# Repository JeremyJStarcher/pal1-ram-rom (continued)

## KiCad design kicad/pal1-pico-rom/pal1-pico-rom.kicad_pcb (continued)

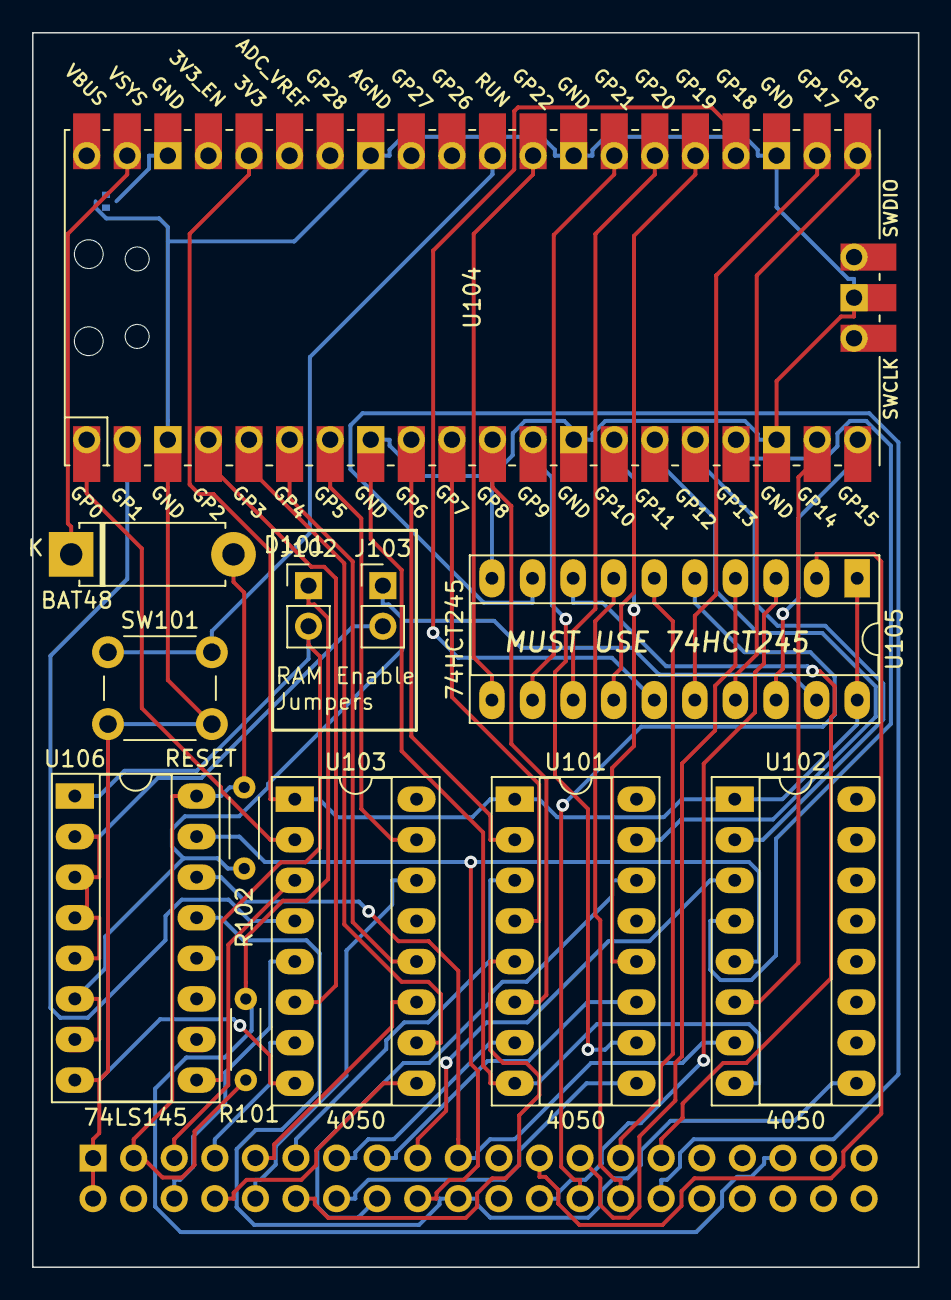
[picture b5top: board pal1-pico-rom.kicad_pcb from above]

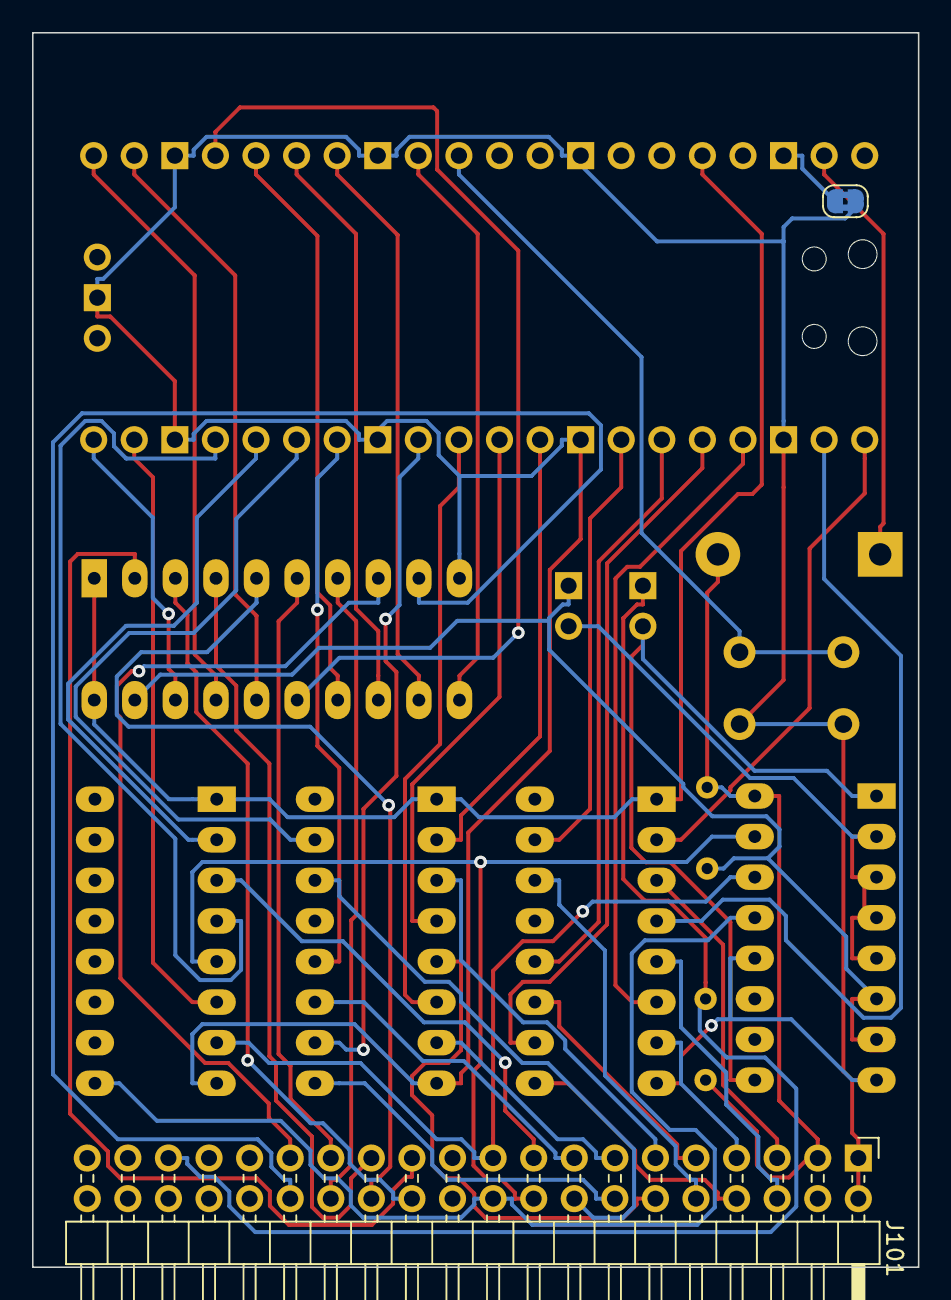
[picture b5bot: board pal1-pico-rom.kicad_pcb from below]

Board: 2 copper layers, 55.4 x 77.3 mm, 14 parts (2 on the bottom side), 57 nets.

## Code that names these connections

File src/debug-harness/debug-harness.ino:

String a;

#define ARRAY_SIZE(arr) (sizeof(arr) / sizeof((arr)[0]))

const int ADDR_LOW = 0x2000;
const int ADDR_HIGH = 0xFFF0;

#define TEST_LSB
#define TEST_MSB
#define TEST_WRITE

const int AA0 = 52;
const int AA1 = 53;

const int AA2 = 50;
const int AA3 = 51;

const int AA4 = 48;
const int AA5 = 49;

const int AA6 = 46;
const int AA7 = 47;

const int AA8 = 44;
const int AA9 = 45;

const int AA10 = 42;
const int AA11 = 43;

const int AA12 = 40;
const int AA13 = 41;

const int AA14 = 38;
const int AA15 = 39;

// R/W which the CPU sets high to read and low to write.
const int RW = 36;
const int PHI2 = 37;

const int DATA0 = 34;
const int DATA2 = 32;
const int DATA4 = A8;
const int DATA6 = 28;

const int DATA1 = 35;
const int DATA3 = 33;
const int DATA5 = 31;
const int DATA7 = 29;

const int RESET = A0;
const int PHI1 = A1;
const int IO3 = A2;
const int DEN = A3;
const int NMI = A4;
const int SYNC = A5;

const int IRQ = 7;
const int ZPB7 = 6;
const int SST = 5;
const int TAPE = 4;
const int RDY = 3;

const int address_lines[] = { AA0, AA1, AA2, AA3, AA4, AA5, AA6, AA7, AA8, AA9, AA10, AA11, AA12, AA13, AA14, AA15 };
const int data_lines[] = { DATA0, DATA1, DATA2, DATA3, DATA4, DATA5, DATA6, DATA7 };

void readString() {
  while (!Serial.available()) {
  }
  while (Serial.available()) {
    a = Serial.readString();  // read the incoming data as string
    //Serial.println(a);
  }
}

uint8_t slowRead(int pin) {
  uint8_t v;
  //delay(100);
  v = digitalRead(pin);
  //delay(100);
  return v;
}

uint8_t readDataPins() {
  uint8_t value = 0;
  uint8_t v;
  for (int i = 0; i < ARRAY_SIZE(data_lines); i++) {
    int pin = data_lines[i];
    pinMode(pin, INPUT);
    v = slowRead(pin);
    value |= v << i;
  }
  return value;
}


uint16_t readAddressPins() {
  set_data_lines_direction(INPUT);

  uint16_t value = 0;
  for (int i = 0; i < ARRAY_SIZE(address_lines); i++) {
    value |= (digitalRead(address_lines[i]) << i);
  }
  return value;
}

void writeDataToPins(uint8_t value) {
  for (int i = 0; i < ARRAY_SIZE(data_lines); i++) {
    int pin = data_lines[i];
    pinMode(pin, OUTPUT);
    digitalWrite(pin, value & (1 << i) ? HIGH : LOW);
    //delay(1 * 1000);
  }
}

void writeAddressToPins(uint16_t value) {
  for (int i = 0; i < ARRAY_SIZE(address_lines); i++) {
    digitalWrite(address_lines[i], value & (1 << i) ? HIGH : LOW);
  }
}

void set_address_lines_direction(int mode) {
  for (size_t i = 0; i < ARRAY_SIZE(address_lines); i++) {
    pinMode(address_lines[i], mode);
  }
}

void set_data_lines_direction(int mode) {
  for (size_t i = 0; i < ARRAY_SIZE(data_lines); i++) {
    int pin = data_lines[i];
    pinMode(pin, mode);
  }
}

void dump_addr_data(int addr, int data) {
  Serial.print("ADDR = ");
  Serial.print(addr, HEX);
  Serial.print(" Data = ");
  Serial.print(data, HEX);
  Serial.print(" ");
  Serial.print(data, BIN);

  Serial.print(" MATCH? ");
  Serial.print(addr & 0x00FF, HEX);

  Serial.println();
}

void reset_pins() {
  set_address_lines_direction(OUTPUT);
  set_data_lines_direction(INPUT);

  pinMode(DEN, INPUT);
  pinMode(RW, OUTPUT);
  pinMode(PHI2, OUTPUT);
  digitalWrite(RW, HIGH);
}

uint8_t read_data(uint16_t addr) {
  digitalWrite(PHI2, LOW);
  writeAddressToPins(addr);
  digitalWrite(PHI2, HIGH);
  uint8_t data = readDataPins();
  return data;
}

void setup() {
  uint8_t data;
  uint8_t is_match;

  //Initialize serial and wait for port to open:
  Serial.begin(9600);
  while (!Serial) {
    ;  // wait for serial port to connect. Needed for native USB port only
  }

  delay(1 * 1000);

  Serial.println();
  Serial.println("====RESET===");
  reset_pins();

#ifdef TEST_LSB
  reset_pins();
  Serial.println("LOAD LSB INTO RAM AND PRESS ENTER");
  readString();
  Serial.println("RUNNING LSB TEST");
  for (int addr = ADDR_LOW; addr < ADDR_HIGH; addr += 1) {
    data = read_data(addr);
    is_match = (addr & 0x00FF) == data;
    if (!is_match) {
      Serial.print("LSB ");
      dump_addr_data(addr, data);
    }
  }
#endif


#ifdef TEST_MSB
  reset_pins();
  Serial.println("LOAD MSB INTO RAM AND PRESS ENTER");
  readString();
  Serial.println("RUNNING MSB TEST");
  for (int addr = ADDR_LOW; addr < ADDR_HIGH; addr += 1) {
    data = read_data(addr);
    is_match = (addr & 0xFF00) == data << 8;
    if (!is_match) {
      Serial.print("MSB ");
      dump_addr_data(addr, data);
    }
  }
#endif

#ifdef TEST_WRITE
  reset_pins();
  Serial.println("RUNNING WRITE TEST");
  for (int addr = ADDR_LOW; addr < ADDR_HIGH; addr += 1) {
    int flipped = ~(addr)&0x00FF;
    digitalWrite(PHI2, LOW);
    digitalWrite(RW, LOW);
    writeAddressToPins(addr);
    writeDataToPins(flipped);

    digitalWrite(PHI2, HIGH);
    digitalWrite(RW, HIGH);

    data = readDataPins();

    if (data != flipped) {
      Serial.print("FLIP TEST ");
      dump_addr_data(addr, data);
    }
  }
#endif

  Serial.println("<-- DONE -->");
}


void loop() {
}

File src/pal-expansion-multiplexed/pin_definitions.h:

// Don't change the pin definitions.
// Optimizations expect that they are in these positions.

// Address pins.
#define A0 0   // 0
#define A1 1   // 1
#define A2 2   // 12
#define A3 3   // 2
#define A4 4   // 3
#define A5 5   // 4
#define A6 6   // 5
#define A7 7   // 6
#define A8 8   // 7
#define A9 9   // 8
#define A10 10  // 9
#define A11 11  // 10
#define A12 12  // 11
#define A13 13  // 13
#define A14 14  // 14
#define A15 15  // 15

// Data pins.
#define D0 0
#define D1 1
#define D2 2
#define D3 3
#define D4 4
#define D5 5
#define D6 6
#define D7 7

#define DATA_DIR 16
#define DATA_CE 17
#define ADDR_CE 18
// #define CS1 9
// #define CS2 10
// #define CS3 11
// #define CS4 12

#define WE 27
#define DEN 28
#define PHI2 26

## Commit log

2024-03-08 Updated code so that CS works correctly, started next PCB version
2024-03-08 Created and added real ROM imagine to run
2024-03-09 Rom code debug tweaks
2024-03-09 RAM working and updating. PHI2 respected.
2024-03-09 Added ROM flag to make ROM areas read-only
2024-03-09 Added USB IO and flash memory support
2024-03-10 Reorganized the code preparing to add save to FLASH
2024-03-10 Bit of PCB cleanup for removed features.
2024-03-10 Moved/addedsome ptp files for testing
2024-03-10 Added bitmasks in binary to the opening panel and added paper tape loading
2024-03-10 Cleaned up commands to upper case, added address decoding test support
2024-03-11 Updated the docs a little. added a data sheet
2024-03-11 New PCB that is 100% software defined
2024-03-11 Got the DECEN working via softwre alone
2024-03-11 moved memory into a broader system-state structure.
2024-03-12 Having load and saving of configuration semi-working
2024-03-12 Moved directories to reflext new home
2024-03-12 Reworked build process to be simplier
2024-03-12 Removed temporary build files
2024-03-12 Removed build artifacts
2024-03-12 More file cleanup
2024-03-12 Added more datasheets
2024-03-12 Swapped cores so that CORE1 can shut down during flashing
    The flashing requires interrupts and the easiest (only?) way to
    shut down interrupts on CORE1 is to reset it back to the default
    state of not running anything.
2024-03-13 Loading/saving and listing of saved files complete.
2024-03-13 Added comments about pause
2024-03-13 Added formatting.
2024-03-13 Removed old media pictures
2024-03-14 Fixed a build error that somehow snuck in
2024-03-14 Made the run-copy script more robust
2024-03-14 The address ranges are now fully software selectable.
2024-03-15 renamed set_ram_byte and set_rom_byte to pokeram and pokerom. added dpokeram, dpokerom
2024-03-15 RAM card input translated to upper case.
2024-03-16 Started adding xmodem support
2024-03-16 Fixed up PCB design due to flat in last PCB
2024-03-16 Various files that never got checked in
2024-03-16 Resolved issue of RAM getting corrupted and unsable
2024-03-16 Code reformat
2024-03-16 The card firmware XMODEM RECIEVE is working and basic may be uploaded.
2024-03-17 Some code cleanup of end of lines in sent strings
    Removed some dead comments/code
2024-03-17 Timer/IO regions excluded from being shadowed. All RAM now shadowed.
2024-03-17 The save to flash function can not have its name changed.
2024-03-17 Removed old version of PCB
2024-03-17 Added a level shifted version
2024-03-20 New board prepared with the level shifters in place
2024-03-21 Updated the PCB to use the old (normal) pin numberings and ordered the board
2024-03-22 Set to the highest optimization rating
2024-03-22 Cleaned up some code to straigten things out
2024-03-22 Set a lower clock speed
2024-03-22 Added a memmap command to show how memory is being used.
2024-03-22 Code cleanup.
2024-03-22 Code cleanup, renamed commands
2024-03-22 Added POKE and DPOKE commands. Fixed range error in memmap display
2024-03-23 Rewrote the pokeram function to be fully bit position aware
2024-03-23 Added PEEK/DPEEK
2024-03-23 Better handling of the RAM/ROM tokens
2024-03-23 Added basic RIOT timer test baseline
2024-03-24 Added basic RIOT timer support but it is too slow to be reliable.
2024-03-24 Bunch of changes to try to get the timer to quit locking up -- none worked.
2024-03-25 Re-enabled 400Mhz - inlined riot timer write
2024-03-25 Isolated the RIOT timer code and workedon a lower clock speed
2024-03-26 Added flags to disable RAM usage
2024-04-04 Added a board with multiplexed bus lines to experiment
2024-04-04 Hacked at the riot test to make the quick test faster
2024-04-04 Attempted to speed up the RIOT access
2024-04-04 Added more datasheets and references
2024-04-04 PCB for the level shifted version
2024-04-06 Updated files
2024-04-06 Brought back old copy of the RIOT timer / baked test into the pico code
2024-04-06 Got the RIOT timer working well.
2024-04-07 Firmware output now redirected to KIM-1 routines
2024-04-07 New GETCH function that converts to upper case
2024-04-08 GETCH intercepted to force things to upper case
2024-04-08 Disable the PAL1 firmware output if ilink is not running
2024-05-05 Trial of multiplexed code
2024-05-09 Read mode on debug harness fully working
2024-05-09 Cleaned up code. Added read/write test
2025-11-09 Demo breaking change for git merge demo
